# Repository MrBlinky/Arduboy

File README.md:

# Arduboy
Everything for Arduboy, a creditcard size opensource retro handheld.

### board-support
An all in one Arduino IDE package to get started with Arduboy and clone variants.
### cathy
A 3K bootloader for Arduboy and Arduino Leonard, Micro and Esplora.
### Streaming bootloader 
A BadAppledemo streaming image to Arduboy in bootloader mode using the Cathy3K bootloader for Arduboy.
### test-toy
My first app for Arduboy for testing and playing around with the hardware.
### uploader
A simple python script to upload hex files to Arduboy.

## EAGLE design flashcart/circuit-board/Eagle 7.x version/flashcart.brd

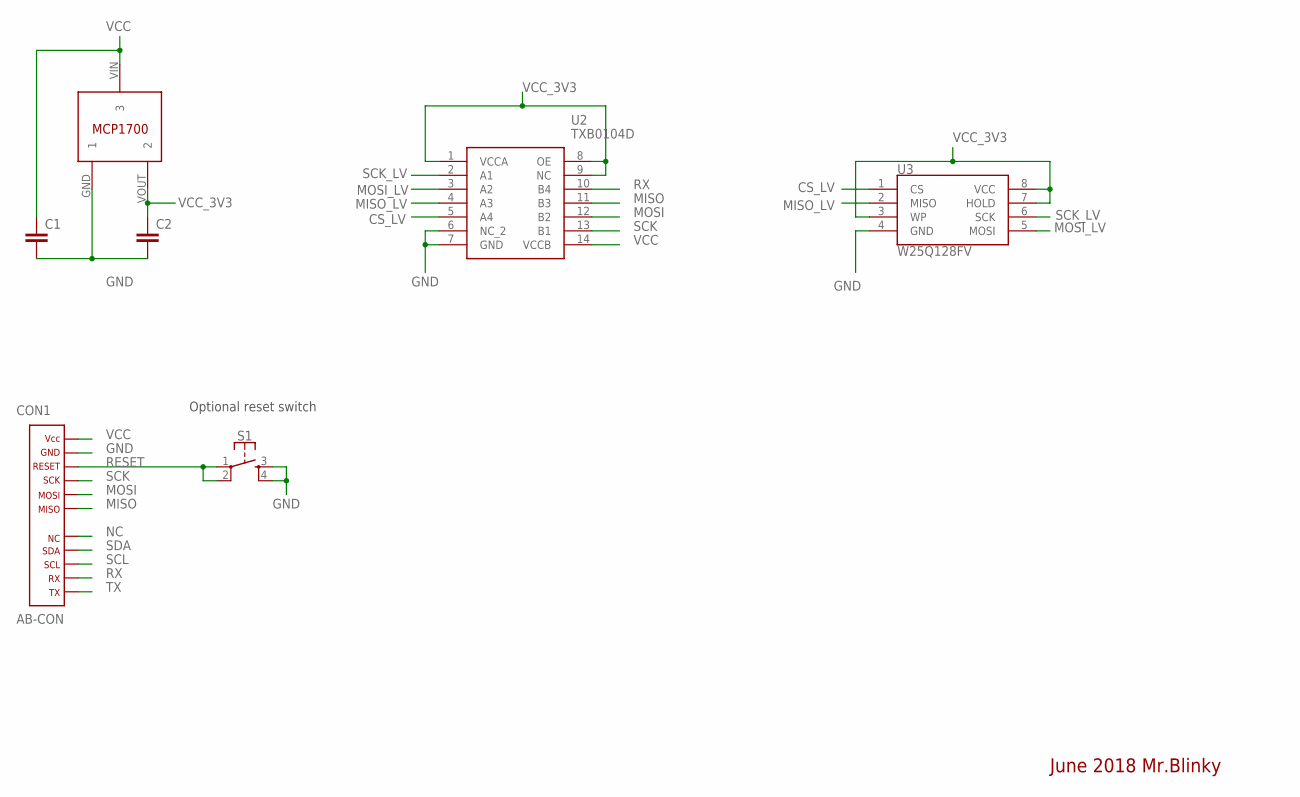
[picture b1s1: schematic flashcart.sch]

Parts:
C1, C2: C-EUC1206; C1206
CON1: AB-CON; CON-PAC
S1: MOMENTARY-SWITCH-SPST-2-SMD-5.2MM; TACTILE_SWITCH_SMD_5.2MM
U1: MCP1700T-3302E/TT
U2: TXB0104D; SOIC127P600X175-14N
U3: W25Q128FV; SO08-EIAJ

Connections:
CS_LV: U2.5 (A4), U3.1 (CS)
GND: C1.2, C2.2, CON1.2, S1.3, S1.4, U1.GND (1), U2.6 (NC_2), U2.7 (GND), U3.4 (GND)
MISO: CON1.6, U2.11 (B3)
MISO_LV: U2.4 (A3), U3.2 (MISO)
MOSI: CON1.5, U2.12 (B2)
MOSI_LV: U2.3 (A2), U3.5 (MOSI)
NC: CON1.8
RESET: CON1.3, S1.1, S1.2
RX: CON1.11, U2.10 (B4)
SCK: CON1.4, U2.13 (B1)
SCK_LV: U2.2 (A1), U3.6 (SCK)
SCL: CON1.10
SDA: CON1.9
TX: CON1.12
VCC: C1.1, CON1.1, U1.VIN (3), U2.14 (VCCB)
VCC_3V3: C2.1, U1.VOUT (2), U2.1 (VCCA), U2.8 (OE), U2.9 (NC), U3.3 (WP), U3.7 (HOLD), U3.8 (VCC)

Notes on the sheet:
June 2018 Mr.Blinky
Optional reset switch

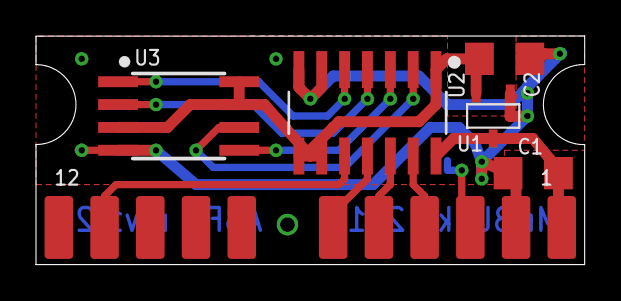
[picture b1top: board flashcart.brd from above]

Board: 2 copper layers, 30.5 x 12.7 mm, 7 parts (1 on the bottom side), 12 nets.

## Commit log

2017-09-16 URL fix
2017-09-17 arduboy library core size reduction
2017-09-17 optimized buttonsState()
2017-09-22 Updated display code in Arduboy and Arduboy2
2017-09-22 Added package and library locations
2017-10-03 Added bootloader overwrite check
2017-10-26 added bootloader com port awareness
2017-10-29 Add files via upload
    Includes Arduboy +1K board and Cathy3K custom Arduboy bootloader
2017-10-29 added v1.1.0
    Arduboy +1K + Cathy3K support
2017-10-29 updated board.txt
    fixed wrong filename for arduboy +1K leonardo bootloader
2017-11-03 Fixed sh1106 display and board.txt issues
2017-11-03 replaced buggy 1.1.0 with v1.1.1
2017-11-03 updated 1.1.0 to 1.1.1
2017-11-03 Deleted buggy version 1.1.0
2017-11-03 Added menu screenshots
2017-11-14 Add files via upload
    Added choice to Warning message
    Used os.sep for multiplatform support
2017-11-14 Update readme.md
    Added PySerial info
2017-11-14 Add files via upload
    Fixed typo added os check for avrdude
2017-11-14 Delete avrdude
    Bad file
2018-01-01 removed unneccesary USB init after power on
    USB was unnecessary initialized when Arduboy hardware is initialized on power on.
    USB is now only initialized in bootloader mode like original Caterina.
2018-01-02 Fixed USB Init glitch
2018-02-14 changed Pro micro wiring
    Changed OLED display reset pin wiring for SparkFun Pro Micro
    Moved LineEncoding to bss section
2018-02-19 MCUSR fix
2018-02-25 fix + optimizer
    Fixed infinite loop on fast bootloader port switching
    Display data is transfered in 1K blocks for faster transfer/better framerate
2018-02-25 infinite loop fix
    Fixed infinite loop on fast bootloader port switching
2018-04-13 Moved to it's own repository
2018-04-13 added (S)NES controller driving button inputs
2018-05-11 Swapped NES A+B, added reset pin
2018-05-13 Added Cathy2K
2018-06-11 added Arduboy flashcart design
2018-06-11 Revert "added Arduboy flashcart design"
    This reverts commit 5d4f50e8c7b9b49be5887b42705178834aeac554.
2018-06-11 Revert "Revert "added Arduboy flashcart design""
    This reverts commit c96a511bbd485223269708772e0fcc00a6746361.
2018-06-11 Revert "Revert "Revert "added Arduboy flashcart design"""
    This reverts commit 879c7f88362d91e13e53ea9f00a002d33526ffdb.
2018-06-11 Added flashcart pcb
2018-06-12 updated Cathy3k to v1.4
2018-06-15 rev1.1 + gerbers
    Changed connector pads, minor tweaks, added Blinky icon, added gerbers
2018-06-17 rev 1.1 update
2018-08-31 added support for ST7565 LCD displays
    added support for ST7565 LCD displays with RGB backlight
2018-10-06 updated board to rev1.2
    Updated board, added manufactured gerbers
2018-10-06 Added rev 1.2 pictures
2018-11-11 Added flashcart test sketch
2018-11-11 Added example flashcart image
2018-11-24 Add support for ArduBigBOY
2018-11-24 Fix line separators
2018-12-04 Remove use of C technique
    C++ doesn't need the C 'typedef' technique.
2018-12-04 Use size_t to represent size
    size_t is the result of the sizeof operator and generally is the best type to represent size and to do indexing with.
2018-12-04 Remove unnecessary default parameter
    Even if this worked from the ,cpp file, it would just cause an ambiguity.
    It either needs to be in the .h file, or using the technique that is currently in use: having a forwarding function.
2018-12-04 Add template functions
    These will automatically infer the size of the array.
2018-12-04 Add space around the assignment operator
2018-12-04 Replace implicit cast with explicit comparison
    Implicit cast to bool can often cause confusion, this is much more explicit.
2018-12-08 Fix comparison bug
    As mentioned in the comments for f411b48, I got the comparison the wrong way round due to only accounting for the implicit cast to bool and not accounting for the following negation.
2018-12-24 Add updated files
2018-12-24 Add greetingcard mode
2019-04-14 add additional animation files
2019-04-14 modified example and library
2019-04-24 update cart class
2019-04-24 fix frames type
    changed frames from uint16_t to __int24
2019-04-26 change type, functions
    using int24_t alias
    change defines to constexpr
    rename readWord to readUInt16
    add readUInt24, readUInt32
    multi byte numbers now bigendian
2019-04-27 update cart.cpp cart.h
    Add functions readUnsave, readEnd, readAheadUInt8
    changed functions readUint... and renamed to readAheadUInt...
2019-04-30 quick update
2019-05-01 change macros, add drawbitmap
    change enableOLED, disableOLED from macro to class functions
    add drawBitmap function
    minor changes
2019-05-01 update sketch for library changes
2019-05-01 add readUnsafeEnd, fix typo in readUnsafe
2019-05-02 add wait, update functions
    add wait
    update readEnd
    optimize seekSata, seekSave, drawBitmap
2019-05-03 add multiplyUInt8 update drawbitmap
2019-05-05 optimize drawbitmap, add fast bitfunctions
    assembly optimized drawbitmap core
    assembly optimized bitfunctions
2019-05-10 add cart detect functions
2019-05-13 add balls demo, update lib, add hex files
    modified readUnsafeEnd function
    add readPendingLast variants of readPending functions
    add experimental getIndexed functions
    add experimental seekDataArray function
    optimize drawBitmap
    fix frame index bug in drawBitmap
2019-05-19 use tilemap for background
2019-05-19 remove debug tag
2019-05-19 add inc/dec visible ball control
2019-06-04 add background control and comments
2019-06-04 Add functions to cart.cpp cart.h
    readBytesEnd
    readDataArray
2019-06-14 add assets
2019-06-15 fix bug in drawbitmap
    fix frame index bug in drawBitmap
2019-11-18 Create LICENSE
2020-07-01 update wiring.c
    Optimized custom timer0 ISR taking the same amount of space as normal C++ version.
2020-07-10 changed button behaviour
    Select button will press UP + DOWN simultaniously (The new Arduboy bootloader trigger)
    Start button will press LEFT + RIGHT simultaniously
2021-02-24 fix corrupt frames in badapple-frames.bin

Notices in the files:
parts and their libraries:
SparkFun-IC-Memory: Licensing: Creative Commons ShareAlike 4.0 International - https://creativecommons.org/licenses/by-sa/4.0
